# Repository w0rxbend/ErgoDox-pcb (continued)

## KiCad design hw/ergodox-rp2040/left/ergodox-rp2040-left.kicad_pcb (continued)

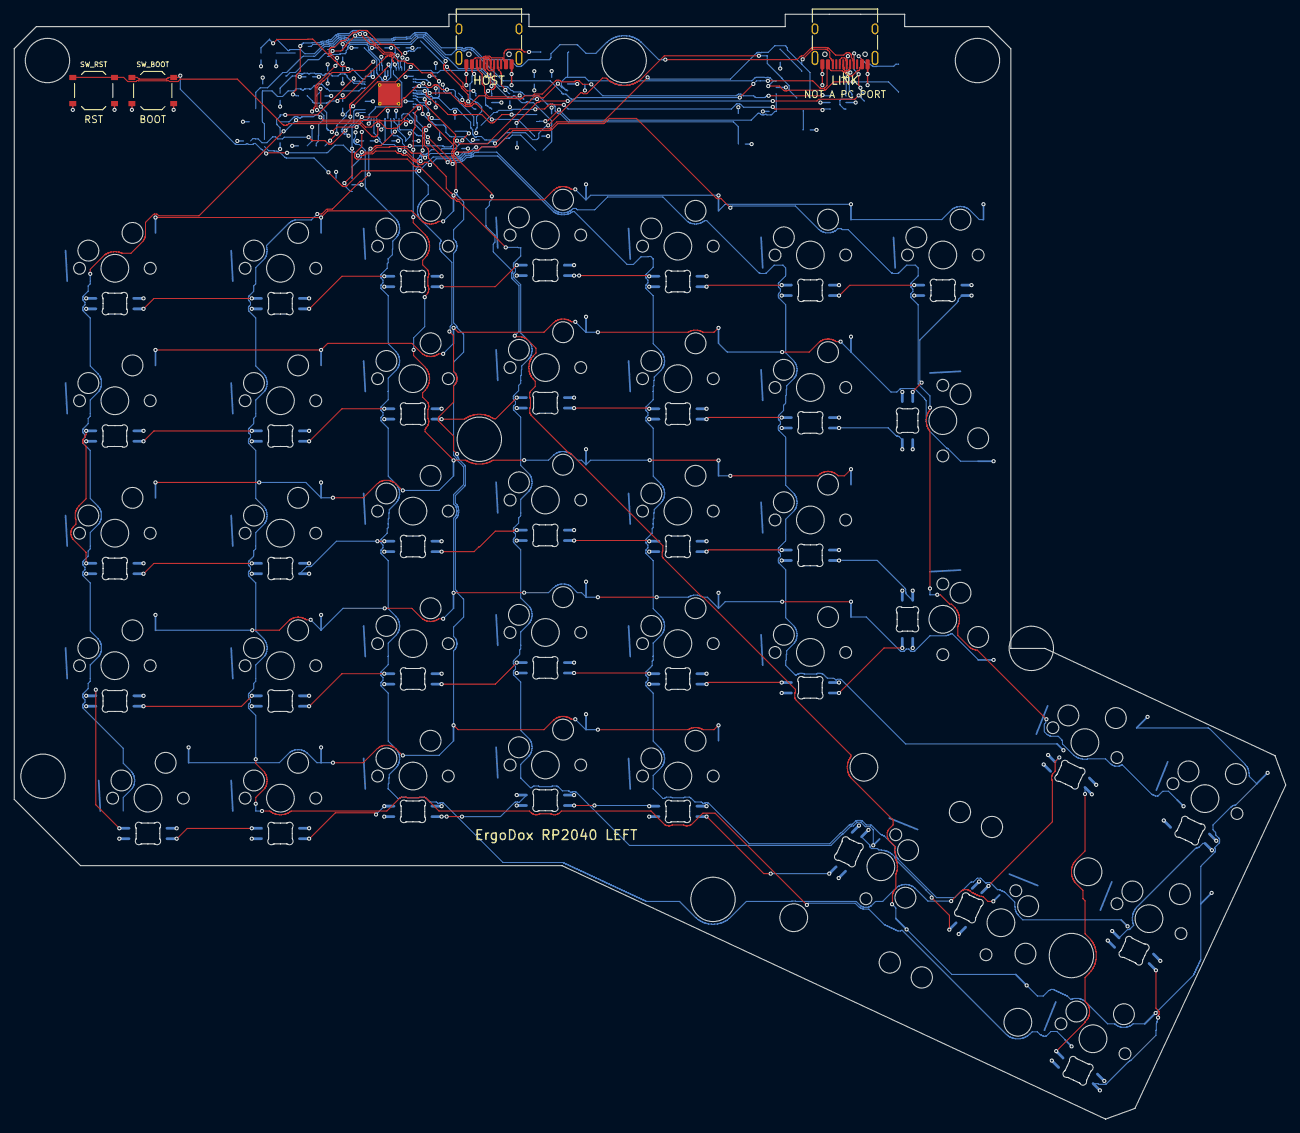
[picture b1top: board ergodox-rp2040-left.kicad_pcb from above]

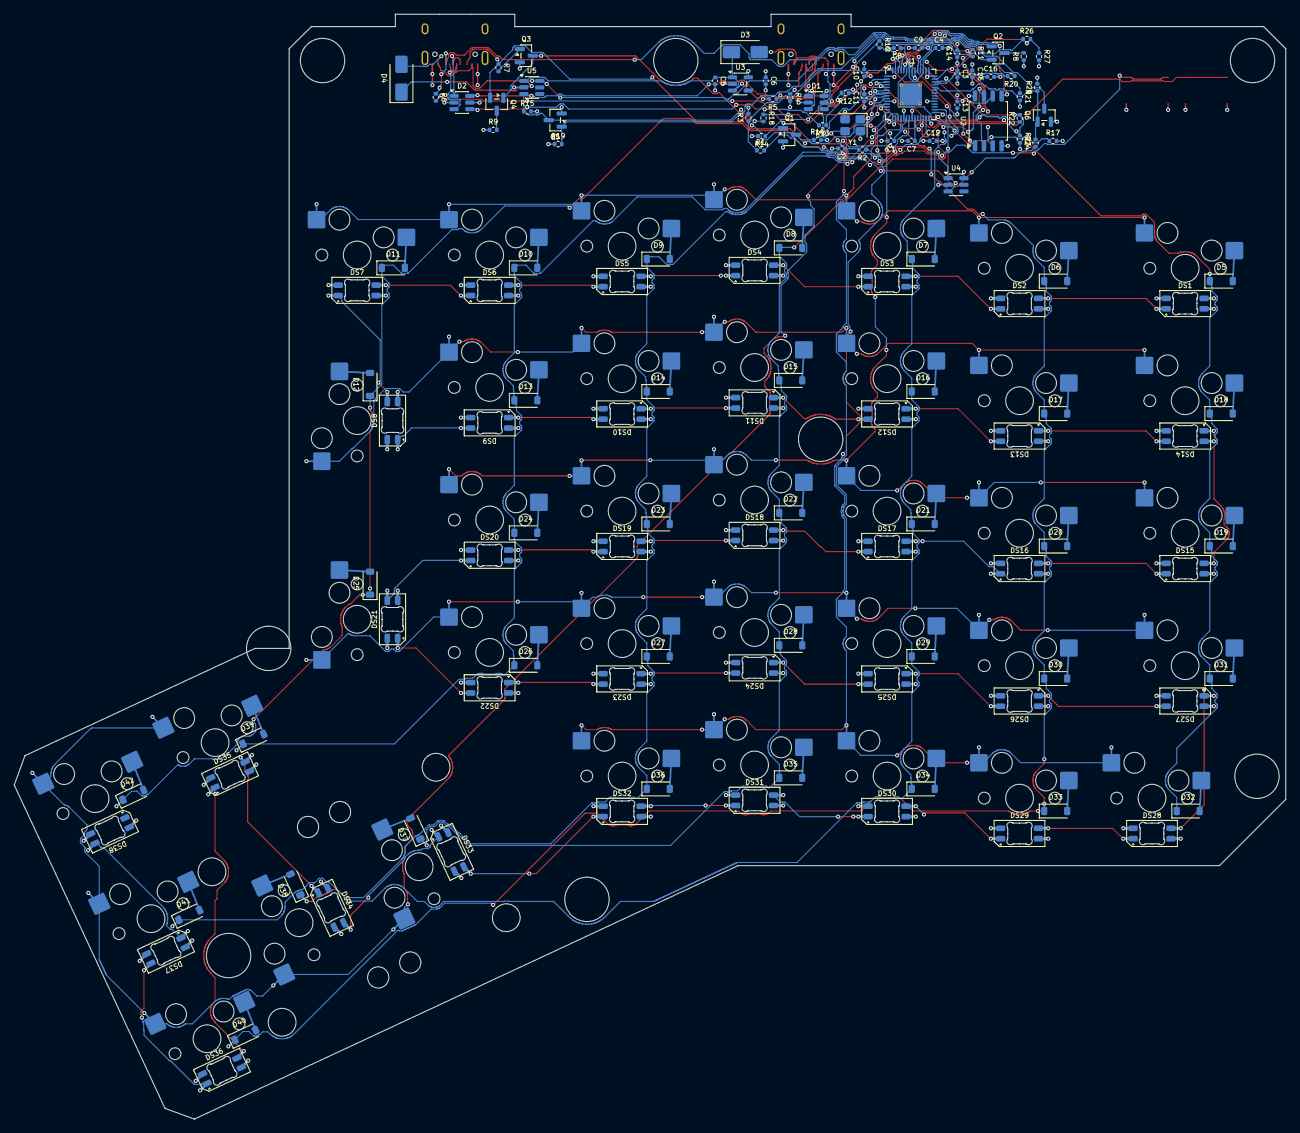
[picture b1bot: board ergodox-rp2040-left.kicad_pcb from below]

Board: 4 copper layers, 182.8 x 158.9 mm, 187 parts (173 on the bottom side), 137 nets.

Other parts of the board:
H1: NPTH; NPTH_H1
H2: NPTH; NPTH_H2
H3: NPTH; NPTH_H3
H4: NPTH; NPTH_H4
H5: NPTH; NPTH_H5
H6: NPTH; NPTH_H6
H7: NPTH; NPTH_H7
H8: NPTH; NPTH_H8
S1: NPTH; NPTH_S1
S2: NPTH; NPTH_S2

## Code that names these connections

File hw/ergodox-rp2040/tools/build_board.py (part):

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"""Generate the left and right ErgoDox RP2040 KiCad 10 schematics.

One circuit. The only intentional differences are the LINK D+/D- UART swap
and the GPIO19 board-id strap (left pulldown, right pullup).
"""

from __future__ import annotations
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		(rev "0.1")
		(comment 1 "Generated by hw/ergodox-rp2040/tools/build_board.py")
		(comment 2 "LINK is a UART cable, not a PC port")
		(comment 3 "Only left/right differences: LINK UART swap and GPIO19 strap")
	)
	(lib_symbols
{lib_text}
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    sheet.assign(mcu, "57", "power", "GND")
    sheet.assign(mcu, "19", "power", "GND")  # TESTEN
    gpio_nets = {
        "2": "GPIO0",
        "3": "GPIO1",
        "4": "LED_DIN",
        "5": "LED_ON",
        "6": "LINK_SRC_REQ",
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    }
    for num, net in gpio_nets.items():
        sheet.assign(mcu, num, "label", net)
    sheet.assign(mcu, "20", "label", "XIN")
    sheet.assign(mcu, "21", "label", "XOUT")
    # Unused GPIO20-25: no pad, no resistor. Firmware turns on the internal pulldown.
    for num in ("31", "32", "34", "35", "36", "37"):
        sheet.assign(mcu, num, "nc", None)
    sheet.assign(mcu, "24", "nc", None)  # SWCLK, test pad not fitted
    sheet.assign(mcu, "25", "nc", None)  # SWDIO
    sheet.assign(mcu, "26", "label", "RUN")
    sheet.assign(mcu, "46", "label", "USB_DM_MCU")
    sheet.assign(mcu, "47", "label", "USB_DP_MCU")
    for num, net in {
        "51": "QSPI_SD3",
        "52": "QSPI_SCLK",
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    # Rebuild D2 explicitly: channel 1 is TX, channel 2 is RX.
    # Undo by not using the computed args. The function already assigned.
    # Verify the nets that were requested:
    # left: conn pin1 = LINK_DP = tx_conn, pin6 = LINK_TX, pin3 = LINK_DM, pin4 = LINK_RX
    # right: tx_conn is LINK_DM, but the call used `tx_conn if left else rx_conn` for pin 1.
    # right: pin1 = rx_conn = LINK_DP, pin6 = LINK_RX, pin3 = tx_conn = LINK_DM, pin4 = LINK_TX.
    # That is the required swap. Good.

    # Schottky OR into +5V. Anode at the connector, cathode at +5V.
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    schottky("D4", "LINK_VBUS")

    # Series 27 ohm next to the RP2040.
    r_part(sheet, "R10", "27", labeled("USB_DP"), labeled("USB_DP_MCU"), note="HOST D+ series, at the RP2040")
    r_part(sheet, "R11", "27", labeled("USB_DM"), labeled("USB_DM_MCU"), note="HOST D- series, at the RP2040")
    r_part(sheet, "R12", "27", labeled("GPIO0"), labeled("LINK_TX"), note="LINK TX series")
    r_part(sheet, "R13", "27", labeled("GPIO1"), labeled("LINK_RX"), note="LINK RX series")

    # HOST CC sink only.
    r_part(sheet, "R4", "5.1k", labeled("HOST_CC1"), powered("GND"), note="HOST CC1 Rd")
    r_part(sheet, "R5", "5.1k", labeled("HOST_CC2"), powered("GND"), note="HOST CC2 Rd")

    # LINK CC, one copy per pin.
    def link_cc(idx, cc_net, sense_net, rd_ref, rp_ref, jfet_ref, nmos_ref, div_top, div_bot):
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                "Note": "Depletion P-channel JFET. On at Vgs=0, off at Vgs=+3.3 V. SOT-23 pad 1 D, 2 S, 3 G.",
            },
        )
        sheet.assign_name(jfet, "G", "label", "LINK_RP_EN")
        sheet.assign_name(jfet, "S", "power", "GND")
        sheet.assign_name(jfet, "D", "label", f"{cc_net}_RD")
        r_part(
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            footprint="Package_TO_SOT_SMD:SOT-23",
            fields={"LCSC": LCSC["2N7002"], "MPN": "2N7002", "Note": "N-channel MOSFET, on at Vgs=3.3 V."},
        )
        sheet.assign_name(nmos, "G", "label", "LINK_RP_EN")
        sheet.assign_name(nmos, "D", "label", f"{cc_net}_RP")
        sheet.assign_name(nmos, "S", "label", cc_net)
        # 200k / 100k. Open-pin load is 300k. 3.3*300/336 = 2.95 V (> 1.65 V).
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    link_cc(1, "LINK_CC1", "CC1_SENSE", "R6", "R8", "Q1", "Q2", "R20", "R21")
    link_cc(2, "LINK_CC2", "CC2_SENSE", "R7", "R9", "Q3", "Q4", "R22", "R23")

    r_part(sheet, "R16", "10k", labeled("LINK_RP_EN"), powered("GND"), note="LINK_RP_EN pulldown")

    # Source-switch gate. ON is shorted to GND unless HOST VBUS is present.
    r_part(sheet, "R18", "1k", labeled("LINK_SRC_REQ"), labeled("LINK_SRC_ON"), note="GPIO series so the clamp MOSFET can win")
    r_part(sheet, "R15", "10k", labeled("LINK_SRC_ON"), powered("GND"), note="LINK source ON pulldown")
    q_gate = sheet.add_part(
        "Transistor_FET:2N7002",
        "Q5",
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        footprint="Package_TO_SOT_SMD:SOT-23",
        fields={"LCSC": LCSC["2N7002"], "MPN": "2N7002", "Note": "Shorts LINK source ON to GND when its gate is high."},
    )
    sheet.assign_name(q_gate, "G", "label", "LINK_GATE")
    sheet.assign_name(q_gate, "D", "label", "LINK_SRC_ON")
    sheet.assign_name(q_gate, "S", "power", "GND")
    r_part(sheet, "R19", "10k", powered("+3V3"), labeled("LINK_GATE"), note="Default-on pull-up for the ON clamp. LCSC is the verified 10k.")
    q_host = sheet.add_part(
        "Transistor_FET:2N7002",
        "Q6",
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        footprint="Package_TO_SOT_SMD:SOT-23",
        fields={"LCSC": LCSC["2N7002"], "MPN": "2N7002", "Note": "Pulls the ON-clamp gate down when HOST VBUS sense is high."},
    )
    sheet.assign_name(q_host, "G", "label", "HOST_VBUS_SENSE")
    sheet.assign_name(q_host, "D", "label", "LINK_GATE")
    sheet.assign_name(q_host, "S", "power", "GND")

    r_part(sheet, "R14", "10k", labeled("LED_ON"), powered("GND"), note="LED switch ON pulldown")

    # VBUS dividers. 100k/100k maps 5.5 V to 2.75 V.
    r_part(sheet, "R24", "100k", labeled("HOST_VBUS"), labeled("HOST_VBUS_SENSE"), note="HOST VBUS divider top. LCSC unverified.")
    r_part(sheet, "R25", "100k", labeled("HOST_VBUS_SENSE"), powered("GND"), note="HOST VBUS divider bottom. LCSC unverified.")
    r_part(sheet, "R26", "100k", labeled("LINK_VBUS"), labeled("LINK_VBUS_SENSE"), note="LINK VBUS divider top. LCSC unverified.")
    r_part(sheet, "R27", "100k", labeled("LINK_VBUS_SENSE"), powered("GND"), note="LINK VBUS divider bottom. LCSC unverified.")

    if side == "left":
        r_part(sheet, "R17", "10k", labeled("BOARD_ID"), powered("GND"), note="Left board id. GPIO19 reads low.")
    else:
        r_part(sheet, "R17", "10k", labeled("BOARD_ID"), powered("+3V3"), note="Right board id. GPIO19 reads high.")

    # Crystal.
    y1 = sheet.add_part(
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        datasheet="https://abracon.com/Resonators/ABM8.pdf",
        fields={"LCSC": LCSC["ABM8-272-T3"], "MPN": "ABM8-272-T3", "Note": "12 MHz, CL 10 pF. Pads 2 and 4 GND."},
    )
    sheet.assign(y1, "1", "label", "XIN")
    sheet.assign(y1, "2", "power", "GND")
    sheet.assign(y1, "3", "label", "XTAL")
    sheet.assign(y1, "4", "power", "GND")
    c_part(sheet, "C1", "15pF", labeled("XIN"), powered("GND"), note="Crystal load, XIN. Chapter value 15 pF.")
    c_part(sheet, "C2", "15pF", labeled("XTAL"), powered("GND"), note="Crystal load, XOUT side of the crystal.")
    r_part(sheet, "R2", "1k", labeled("XOUT"), labeled("XTAL"), note="Crystal damper from XOUT")

    # Buttons.
    two_pin(
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        "SW_RST",
        "TS-1187A-B-A-B",
        "Button_Switch_SMD:SW_Push_1P1T_XKB_TS-1187A",
        labeled("RUN"),
        powered("GND"),
        lcsc_key="TS-1187A-B-A-B",
        fields={"Note": "RESET. RUN to GND. Internal pull-up, no external RUN resistor."},
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        lcsc_key="TS-1187A-B-A-B",
        fields={"Note": "BOOTSEL. Through 1k from QSPI_SS."},
    )
    r_part(sheet, "R1", "1k", labeled("QSPI_SS"), labeled("BOOT"), note="BOOTSEL series")
    r_part(
        sheet,
        "R3",
        "10k",
        labeled("QSPI_SS"),
        powered("+3V3"),
        dnp=True,
        note="DNF. Winbond flash does not need the external CS pull-up.",
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        for need in ("VSS", "DIN", "VDD", "DOUT"):
            if need not in by_name:
                raise RuntimeError(f"SK6812 pins {led['pins']}")
        sheet.assign(led, by_name["VDD"], "label", "LED_5V")
        sheet.assign(led, by_name["VSS"], "power", "GND")
        sheet.assign(led, by_name["DIN"], "label", din)
        if dout is None:
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            sheet.assign(led, by_name["DOUT"], "label", dout)

    swap = "D+ = LINK_TX, D- = LINK_RX" if side == "left" else "D+ = LINK_RX, D- = LINK_TX"
    strap = "GPIO19 10k to GND" if side == "left" else "GPIO19 10k to +3V3"
    notes = [
        f"{side.upper()} half. Silkscreen this board {side.upper()}.",
        "LINK receptacle silkscreen: LINK and NOT A PC PORT. It is not a USB device port.",
        f"UART swap on this half: {swap}. GPIO0 is UART0 TX. GPIO1 is UART0 RX.",
        f"Board id: {strap}. Firmware may read it. It does not select the ZMK role.",
        "ZMK role is compile-time. Flash the central image into the half whose HOST plug is in the computer.",
        "HOST CC pins are Rd 5.1k only. No Rp on HOST. VBUS enters +5V through SS14.",
        "LINK Rp is 36k to +3.3V, one per CC pin, only while LINK_RP_EN is high.",
        "CC divider 200k/100k keeps a 36k open pin at 2.95 V and 5.5 V at 1.83 V on the ADC.",
        "VBUS divider 100k/100k maps 5.5 V to 2.75 V. Divider LCSC codes are blank.",
        "36k, 100k and 200k resistors have no verified LCSC code.",
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        elif compact == "GND" or compact == "VSS":
            out.append((num, "power", "GND"))
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
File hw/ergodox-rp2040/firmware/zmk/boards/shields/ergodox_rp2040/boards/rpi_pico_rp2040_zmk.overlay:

/*
 * Copyright (c) 2026 The ErgoDox RP2040 contributors
 * SPDX-License-Identifier: MIT
 *
 * Applied only for the rpi_pico/rp2040/zmk target. This is not a Pico HAT.
 * The Pico board devicetree is the RP2040 with a 12 MHz crystal and native USB.
 * Overrides below stop the Pico from claiming this PCB's GPIOs.
 *
 * HOST_VBUS_SENSE is GPIO26 / ADC0 through the 100k/100k divider. It stays an
 * ADC pin. ZMK role is compile-time, so this pin is not a gpio-hog and does
 * not select central. CC1, CC2, and LINK VBUS are the other three ADC inputs.
 *
 * LED chain, index 1 first, fed from GPIO2. Same index order on both halves.
 * It starts at the top-row key beside the controller and ends in the thumb cluster.
 * ZMK underglow has no per-key map; the wire order is the order below.
 *  1 SW5:13 ROW5 COL0
 *  2 SW5:12 ROW5 COL1
 *  3 SW5:11 ROW5 COL11
 *  4 SW5:10 ROW5 COL10
 *  5 SW5:9  ROW5 COL4
 *  6 SW5:8  ROW5 COL5
 *  7 SW5:7  ROW5 COL6
 *  8 SW4:7  ROW4 COL6
 *  9 SW4:8  ROW4 COL5
 * 10 SW4:9  ROW4 COL4
 * 11 SW4:10 ROW4 COL10
 * 12 SW4:11 ROW4 COL11
 * 13 SW4:12 ROW4 COL1
 * 14 SW4:13 ROW4 COL0
 * 15 SW3:13 ROW3 COL0
 * 16 SW3:12 ROW3 COL1
 * 17 SW3:11 ROW3 COL11
 * 18 SW3:10 ROW3 COL10
 * 19 SW3:9  ROW3 COL4
 * 20 SW3:8  ROW3 COL5
 * 21 SW2:7  ROW2 COL6
 * 22 SW2:8  ROW2 COL5
 * 23 SW2:9  ROW2 COL4
 * 24 SW2:10 ROW2 COL10
 * 25 SW2:11 ROW2 COL11
 * 26 SW2:12 ROW2 COL1
 * 27 SW2:13 ROW2 COL0
 * 28 SW1:13 ROW1 COL0
 * 29 SW1:12 ROW1 COL1
 * 30 SW1:11 ROW1 COL11
 * 31 SW1:10 ROW1 COL10
 * 32 SW1:9  ROW1 COL4
 * 33 SW0:10 ROW0 COL10
 * 34 SW0:11 ROW0 COL11
 * 35 SW0:8  ROW0 COL5
 * 36 SW0:12 ROW0 COL1
 * 37 SW0:9  ROW0 COL4
 * 38 SW0:7  ROW0 COL6
 *
 * Color order is the ZMK/Zephyr WS2812 example (GRB). The OPSCO SK6812MINI-E channel
 * order was not read from its datasheet. Confirm before the first light-up.
 * Frame bytes and the 4 MHz clock are copied from that example, not retuned.
 */

#include <zephyr/dt-bindings/gpio/gpio.h>
#include <zephyr/dt-bindings/led/led.h>
#include <zephyr/dt-bindings/pinctrl/rpi-pico-rp2040-pinctrl.h>
#include <zephyr/dt-bindings/clock/rpi_pico_rp2040_clock.h>

/ {
    chosen {
        zmk,underglow = &led_strip;
    };
};

/* Pico defaults are already P0/P1. Restated so the pin check sees them. */
&uart0_default {
    group1 {
        pinmux = <UART0_TX_P0>;
    };
    group2 {
        pinmux = <UART0_RX_P1>;
        input-enable;
    };
};

/* Dividers on GPIO26-29. Do not hog these as digital inputs. */
&adc_default {
    group1 {
        pinmux = <ADC_CH0_P26>, <ADC_CH1_P27>, <ADC_CH2_P28>, <ADC_CH3_P29>;
        input-enable;
    };
};

/* Pico i2c0 uses GPIO4/GPIO5, which are LINK_SRC_REQ and LINK_RP_EN. */
&i2c0 {
    status = "disabled";
};

/* Pico spi0 uses GPIO16-19: COL6, COL10, COL11, and BOARD_ID. */
&spi0 {
    status = "disabled";
};

/* Pico user LED and PWM slice are GPIO25, an unused pulldown on this board. */
&led0 {
    status = "disabled";
};

&pwm {
    status = "disabled";
};

&pinctrl {
    ws2812_pio0_default: ws2812_pio0_default {
        group1 {
            pinmux = <PIO0_P2>;
        };
    };
};

&pio0 {
    status = "okay";

    pio0_spi: pio0_spi {
        compatible = "raspberrypi,pico-spi-pio";
        #address-cells = <1>;
        #size-cells = <0>;
        pinctrl-0 = <&ws2812_pio0_default>;
        pinctrl-names = "default";
        clocks = <&clocks RPI_PICO_CLKID_CLK_SYS>;
        clock-frequency = <4000000>;
        /* Data is GPIO2. Clock and MISO are unused pulldowns, not the matrix. */
        mosi-gpios = <&gpio0 2 GPIO_ACTIVE_HIGH>;
        clk-gpios = <&gpio0 20 GPIO_ACTIVE_HIGH>;
        miso-gpios = <&gpio0 21 GPIO_ACTIVE_HIGH>;
        status = "okay";

        led_strip: ws2812@0 {
            compatible = "worldsemi,ws2812-spi";
            reg = <0>;
            chain-length = <38>;
            spi-max-frequency = <4000000>;
            spi-one-frame = <0x70>;
            spi-zero-frame = <0x40>;
            color-mapping = <LED_COLOR_ID_GREEN LED_COLOR_ID_RED LED_COLOR_ID_BLUE>;
            status = "okay";
        };
    };
};
